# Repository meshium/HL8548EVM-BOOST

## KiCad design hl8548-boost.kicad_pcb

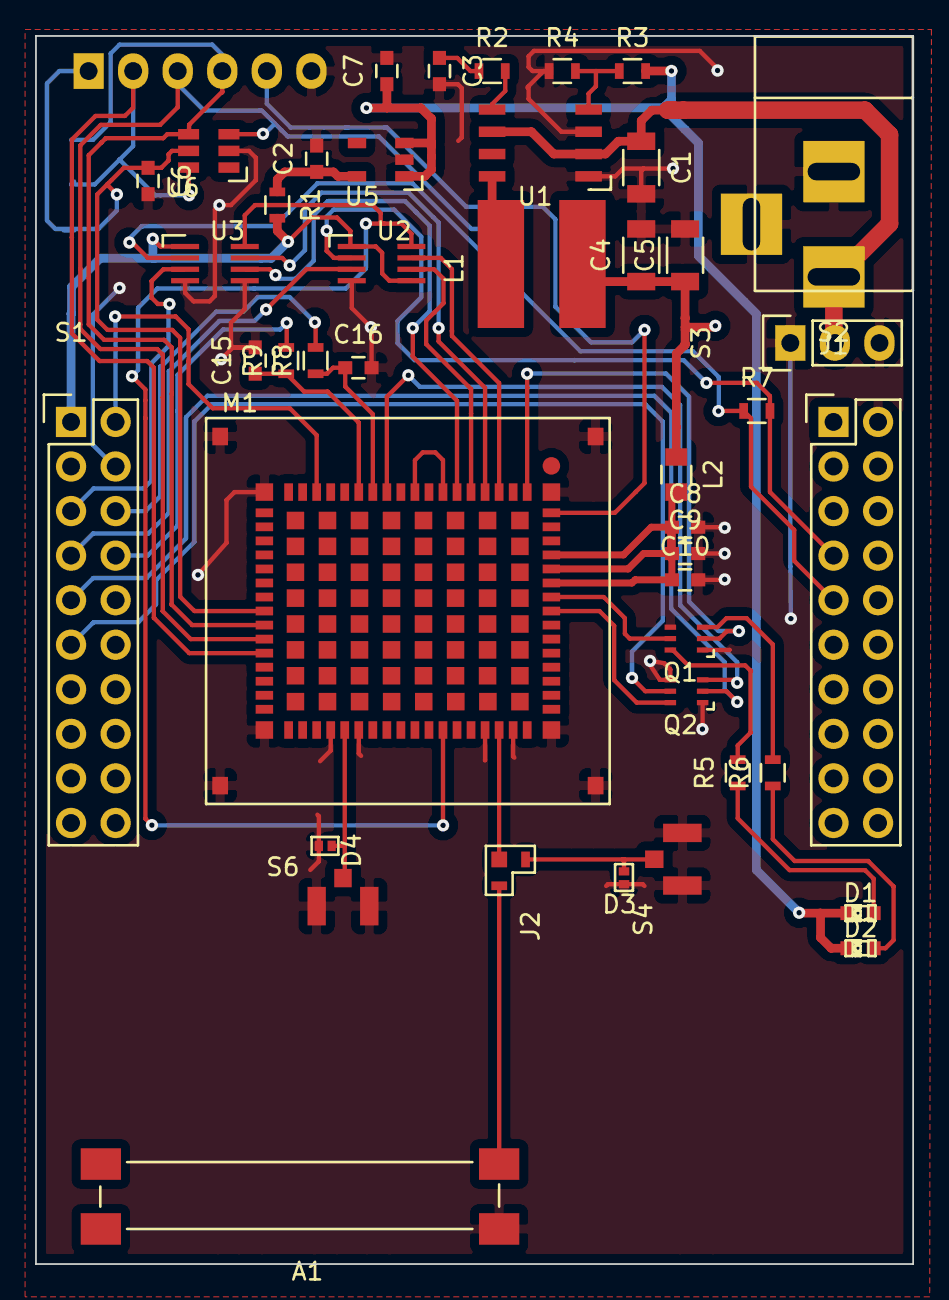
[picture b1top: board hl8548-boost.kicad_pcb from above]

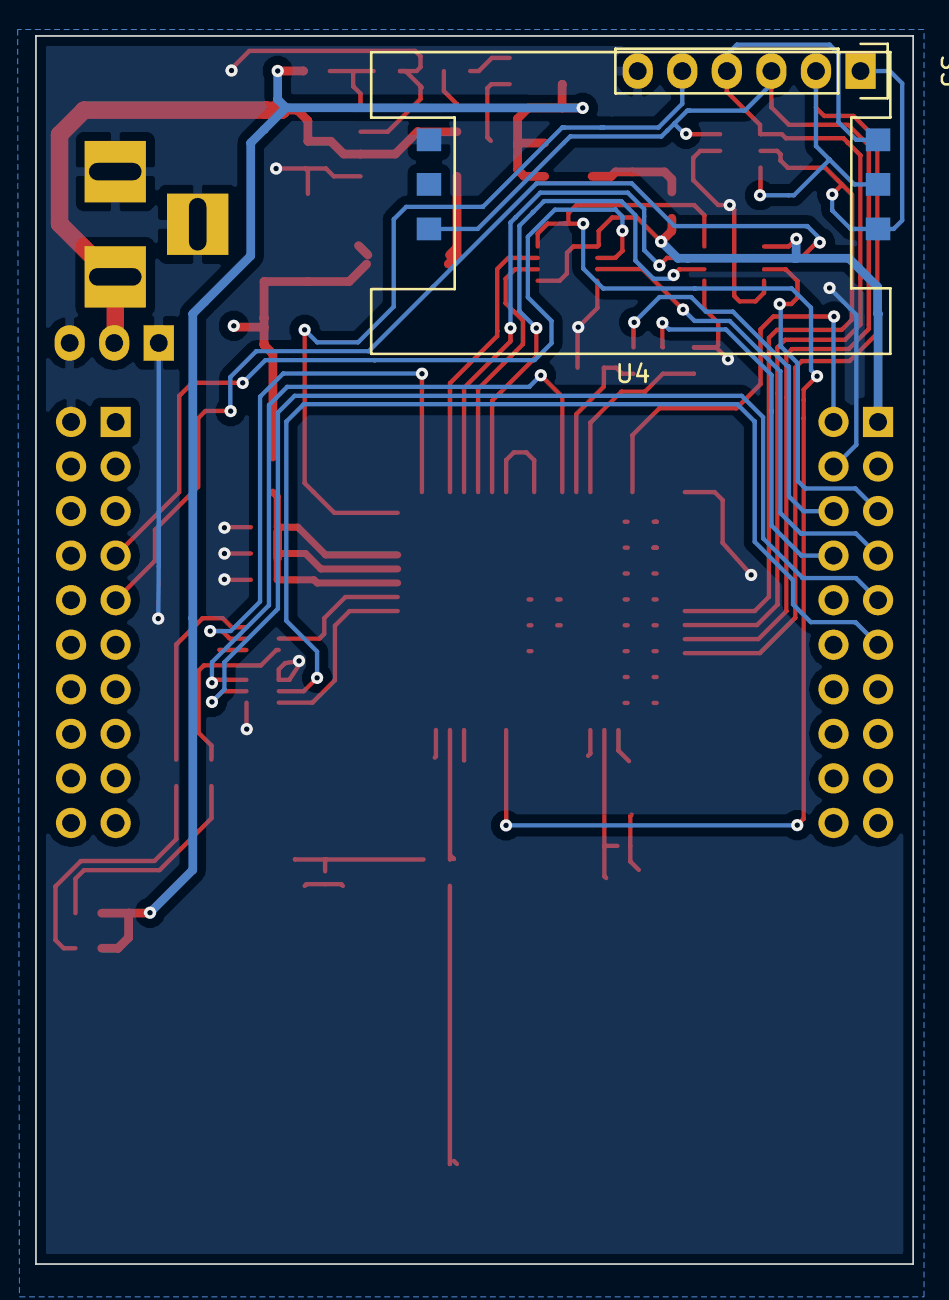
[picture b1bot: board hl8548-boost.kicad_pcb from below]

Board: 2 copper layers, 50.0 x 70.0 mm, 45 parts (2 on the bottom side), 44 nets.

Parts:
A1: AMMAP004
C1, C4, C5: 22uF; C_1206
C2, C7: 1uF; C_0603
C3: 1.5nF; C_0603
C6: 0.1uF; C_0603
C8: 10uF; C_0603
C9: 0.01uF; C_0603
C10: 30pF; C_0603
C15, C16: 0.22uF; C_0603
D1, D2: LED_small; LED-0603
D3, D4: ESD7471; SOD-882
J1: BARREL_JACK
J2: JP3
L1: 3.3uH; CDRH6D38NP
L2: BLM21PG221SN1D; C_0805
M1: HL8548; LGA-234
Q1, Q2: MUN5211DW; SOT-363
R1, R7: 0; R_0603
R2: 12.1K; R_0603
R3: 62K; R_0603
R4: 15K; R_0603
R5, R6: R; R_0603
R8, R9: 22R; R_0603
S1, S2: CONN_02X10; Pin_Header_Straight_2x10
S3: CONN_01X03; Pin_Header_Straight_1x03
S4, S6: IPEX-20279-001E-01
S5: CONN_01X06; Pin_Header_Straight_1x06
U1: NCP3170; SOIC8
U2, U3: SN74LVC2T45DCT; SSOP-8
U4: ATOM010050030052
U5: TPS76333; SOT23-5
U6: USBLC6-4; SOT23-6L

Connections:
CTS: R7.1, S2.9, U3.2
GND: A1.1, C1.2, C2.2, C3.2, C4.2, C5.2, C6.2, C7.2, C8.2, C9.2, C10.2, C15.2, C16.2, D3.1, D4.2, J1.2, J1.3, M1.37, M1.39, M1.48, M1.50, M1.67, M1.68, M1.69, M1.70, M1.167, M1.168, M1.169, M1.170, Q1.1, Q1.4, Q2.1, Q2.4, R4.1, S1.4, S2.2, S3.1, S3.3, S4.2, S4.3, S5.6, S6.2, S6.3, U1.1, U1.3, U2.4, U3.4, U3.5, U4.4, U5.2, U6.2
unnamed: A1.2, J2.2
unnamed: C1.1, J1.1, S3.2, U1.2, U1.6
unnamed: C2.1, R1.1, U5.5
unnamed: C3.1, R2.1
unnamed: C4.1, C5.1, C7.1, D1.1, D2.1, L1.2, L2.1, R3.2, U5.1, U5.3
unnamed: C6.1, M1.26, S5.1, U4.1, U6.5
unnamed: C8.1, C9.1, C10.1, L2.2, M1.61, M1.62, M1.63
unnamed: C15.1, M1.13, R9.1
unnamed: C16.1, M1.12, R8.1
unnamed: D1.2, R5.1
unnamed: D2.2, R6.1
unnamed: D3.2, J2.3, S4.1
unnamed: D4.1, M1.38, S6.1
unnamed: J2.1, M1.49
unnamed: L1.1, U1.8
unnamed: M1.1, Q1.2
unnamed: M1.3, U2.7
unnamed: M1.4, U3.7
unnamed: M1.5, U2.6
unnamed: M1.6, U3.6
unnamed: M1.7, M1.9
unnamed: M1.11, Q2.3
unnamed: M1.16, S1.2
unnamed: M1.27, S5.4, U4.3, U6.4
unnamed: M1.28, S5.3, U4.6, U6.3
unnamed: M1.29, S5.2, U4.2, U6.6
unnamed: M1.45, U2.8, U3.8
unnamed: M1.59, Q2.6
unnamed: M1.60, Q1.5
unnamed: Q1.3, R6.2
unnamed: Q1.6, R5.2
unnamed: R1.2, S1.1, U2.1, U2.5, U3.1
unnamed: R2.2, U1.5
unnamed: R3.1, R4.2, U1.4
unnamed: R8.2, S1.6
unnamed: R9.2, S1.8
PWR_ON: Q2.2, S1.9
RES: Q2.5, S1.11
RTS: R7.2, S2.7, U2.2
RXD: S1.5, U3.3
SIM_SEL: M1.66, S5.5
TXD: S1.7, U2.3

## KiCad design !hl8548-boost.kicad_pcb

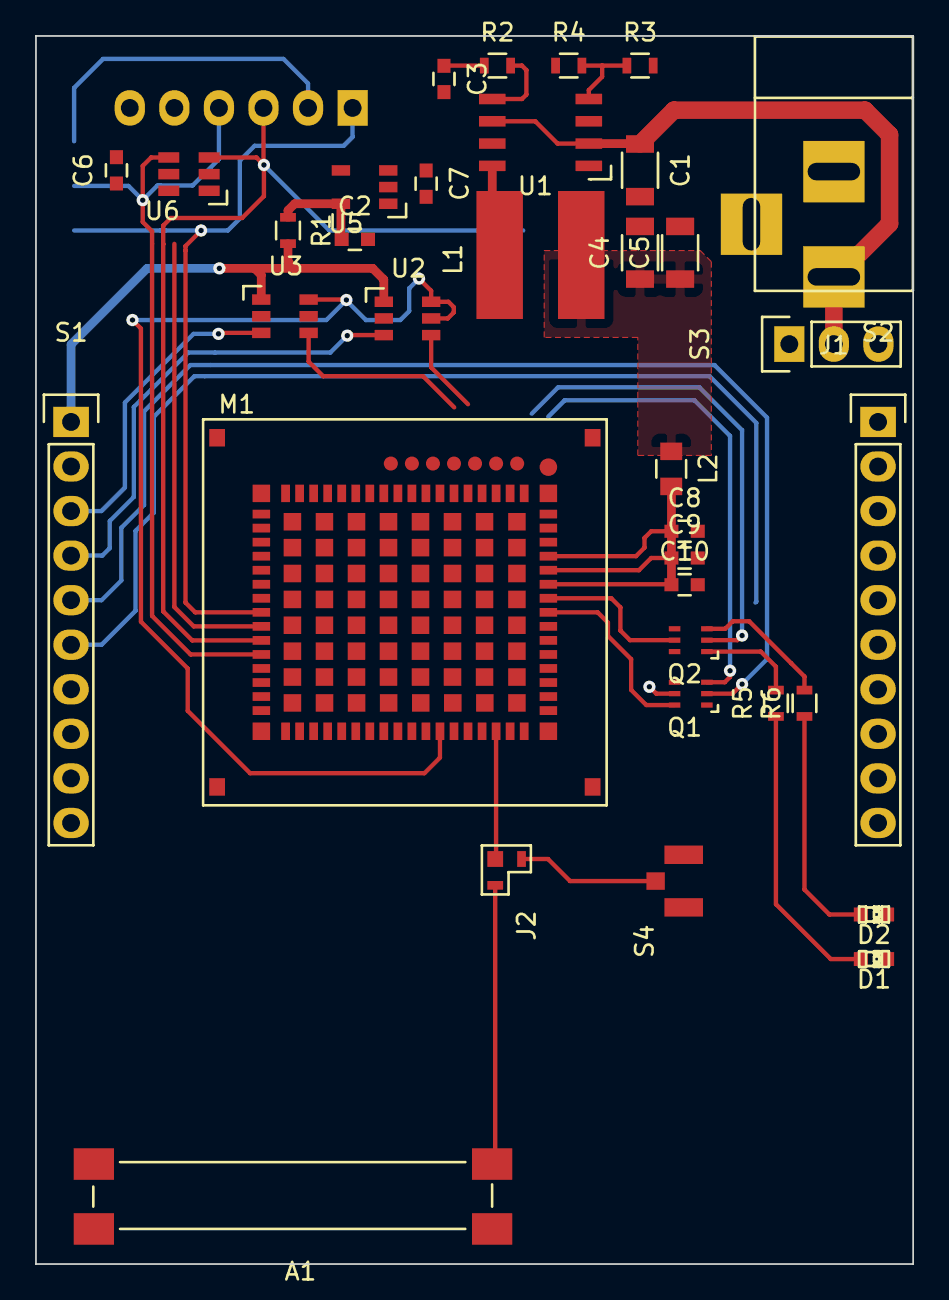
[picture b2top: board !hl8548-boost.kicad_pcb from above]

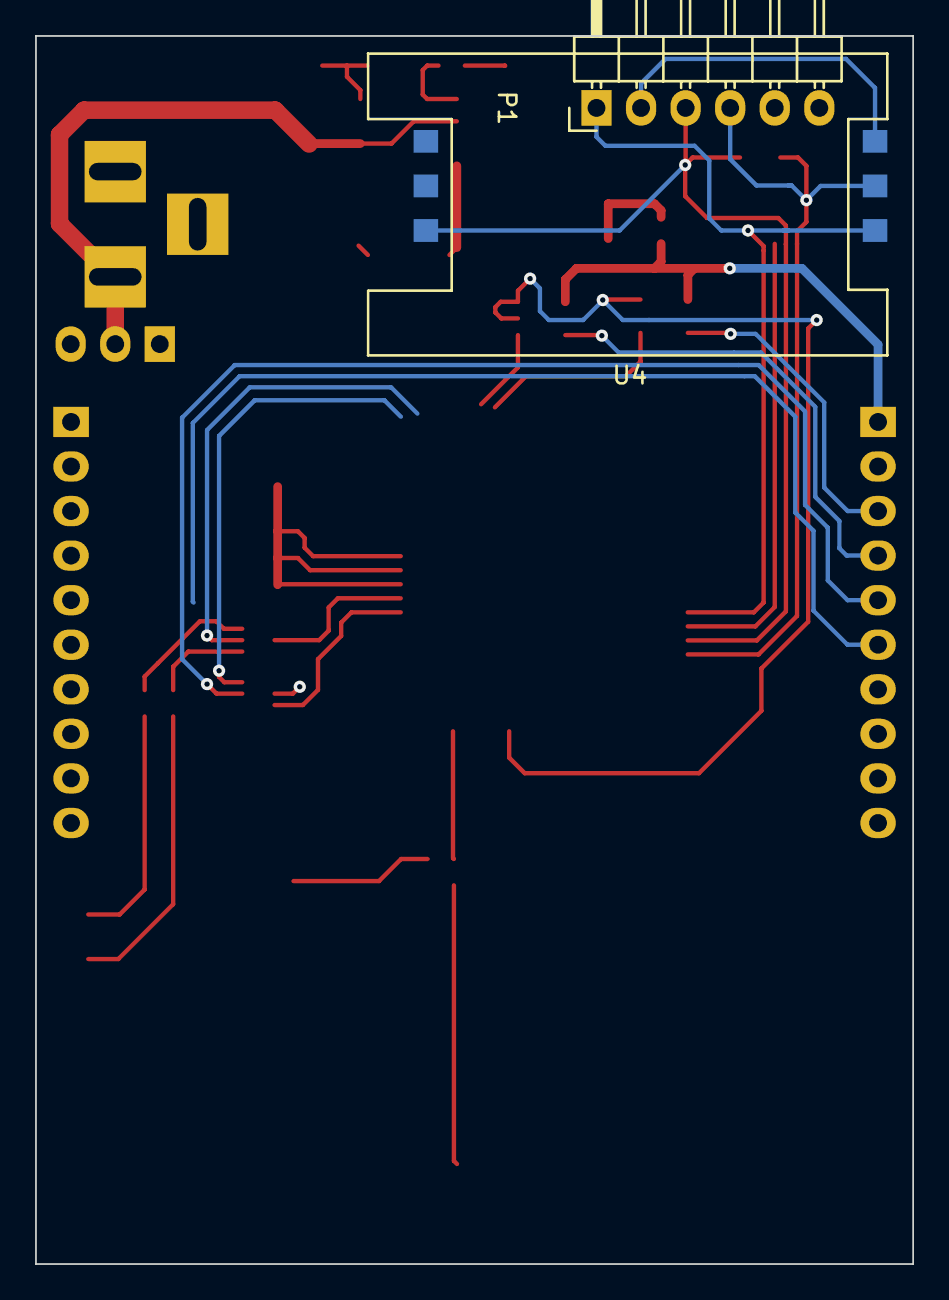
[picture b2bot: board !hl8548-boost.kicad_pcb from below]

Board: 2 copper layers, 50.0 x 70.0 mm, 37 parts (2 on the bottom side), 34 nets.

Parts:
A1: AMMAP004
C1, C4, C5: 22uF; C_1206
C2, C6, C7: 1uF; C_0603
C3: 1.5nF; C_0603
C8: 10uF; C_0603
C9: 0.01uF; C_0603
C10: 30pF; C_0603
D1, D2: LED_small; LED-0603
J1: BARREL_JACK
J2: JP3
L1: 3.3uH; CDRH6D38NP
L2: BLM21PG221SN1D; C_0805
M1: HL8548; LGA-234
P1: CONN_01X06; Pin_Header_Angled_1x06
Q1, Q2: MUN5211DW; SOT-363
R1: 0; R_0603
R2: 12.1K; R_0603
R3: 62K; R_0603
R4: 15K; R_0603
R5, R6: R; R_0603
S1, S2: CONN_01X10; Pin_Header_Straight_1x10
S3: CONN_01X03; Pin_Header_Straight_1x03
S4: IPEX-20279-001E-01
U1: NCP3170; SOIC8
U2, U3: SN74LVC1T45DBVR; SOT23-6
U4: ATOM010050030052
U5: TPS76333; SOT23-5
U6: USBLC6-4; SOT23-6L

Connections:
/PWR_ON: Q1.2, S1.5
/RES: Q1.5, S1.6
/RXD: S1.3, U3.3
/TXD: S1.4, U2.3
/VCC_LP: R1.2, S1.1, U2.1, U3.1
GND: A1.1, C1.2, C2.2, C3.2, C4.2, C5.2, C6.2, C7.2, C8.2, C9.2, C10.2, J1.2, J1.3, M1.37, M1.39, M1.48, M1.50, M1.67, M1.68, M1.69, M1.70, M1.235, P1.6, Q1.1, Q1.4, Q2.4, Q2.6, R4.1, S2.1, S3.1, S3.3, S4.2, S4.3, U1.1, U1.3, U2.2, U3.2, U3.5, U4.4, U5.2, U6.2
unnamed: A1.2, J2.2
unnamed: C1.1, J1.1, S3.2, U1.2, U1.6
unnamed: C2.1, R1.1, U5.5
unnamed: C3.1, R2.1
unnamed: C4.1, C5.1, C7.1, D1.1, D2.1, L1.2, L2.1, R3.2, U5.1, U5.3
unnamed: C6.1, M1.26, P1.1, U4.1, U6.5
unnamed: C8.1, C9.1, C10.1, L2.2, M1.61, M1.62, M1.63
unnamed: D1.2, R5.1
unnamed: D2.2, R6.1
unnamed: J2.1, M1.49
unnamed: J2.3, S4.1
unnamed: L1.1, U1.8
unnamed: M1.1, Q2.2
unnamed: M1.3, M1.4
unnamed: M1.5, U2.4
unnamed: M1.6, U3.4
unnamed: M1.7, M1.9
unnamed: M1.11, Q1.3
unnamed: M1.27, P1.2, U4.3, U6.1
unnamed: M1.28, P1.3, U4.6, U6.3
unnamed: M1.29, P1.4, U4.2, U6.4
unnamed: M1.45, U2.5, U2.6, U3.6
unnamed: M1.59, Q1.6
unnamed: M1.60, Q2.5
unnamed: Q2.1, R5.2
unnamed: Q2.3, R6.2
unnamed: R2.2, U1.5
unnamed: R3.1, R4.2, U1.4

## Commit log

2015-07-05 Added new file .gitignore
2015-07-06 Just daily commit
2015-07-10 Weekly commit
2015-07-24 Yet another weekly commit
2015-11-12 PCB tracerouting
